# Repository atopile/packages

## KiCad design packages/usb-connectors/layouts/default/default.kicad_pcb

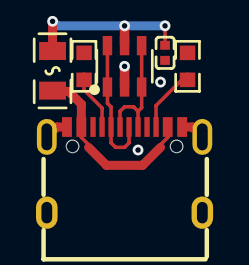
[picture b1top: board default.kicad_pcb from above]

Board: 2 copper layers, 6 parts (0 on the bottom side), 7 nets.

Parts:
C2: 0F; C0402
D1: SOT-23-6_L2.9-W1.6-P0.95-LS2.8-BL
F2: F0805
R1, R2: 10000Ω; R0603
X1: USB-C-SMD_TYPE-C-6PIN-2MD-073

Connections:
4: R1.1, X1.4
10: R2.1, X1.10
DATA_N: D1.1, D1.6, X1.5, X1.7
DATA_P: D1.3, D1.4, X1.6, X1.8
hv: F2.1, X1.2, X1.11
lv: C2.2, D1.2, R1.2, R2.2, X1.1, X1.12, X1.13, X1.14, X1.15, X1.16
power-hv: C2.1, D1.5, F2.2

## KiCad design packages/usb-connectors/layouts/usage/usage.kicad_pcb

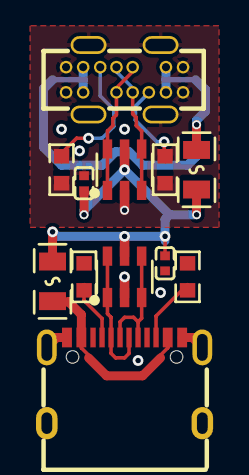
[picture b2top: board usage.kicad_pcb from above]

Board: 2 copper layers, 12 parts (0 on the bottom side), 12 nets.

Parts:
C2, C4: 0F; C0402
D1, D2: SOT-23-6_L2.9-W1.6-P0.95-LS2.8-BL
F2, F4: F0805
R1, R2, R3, R4: 10000Ω; R0603
USB1: USB-C-SMD_TYPE-C-6PIN-2MD-073
USBC1: USB-C-TH_TYPE-C-USB-14P

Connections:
4: R1.1, USB1.4
5: R4.1, USBC1.5
10: R2.1, USB1.10
12: R3.1, USBC1.12
DATA_N: D1.1, D1.6, USB1.5, USB1.7
DATA_P: D1.3, D1.4, USB1.6, USB1.8
connector-power_vbus-hv: F2.1, USB1.2, USB1.11
connector-power_vbus-hv-1: F4.1, USBC1.2, USBC1.6, USBC1.9, USBC1.13
hv: C2.1, C4.1, D1.5, D2.5, F2.2, F4.2
lv: C2.2, C4.2, D1.2, D2.2, R1.2, R2.2, R3.2, R4.2, USB1.1, USB1.12, USB1.13, USB1.14, USB1.15, USB1.16, USBC1.0, USBC1.1, USBC1.7, USBC1.8, USBC1.14, USBC1.15, USBC1.16, USBC1.17
usb_connector_vertical-usb-DATA_N: D2.1, D2.6, USBC1.3, USBC1.10
usb_connector_vertical-usb-DATA_P: D2.3, D2.4, USBC1.4, USBC1.11

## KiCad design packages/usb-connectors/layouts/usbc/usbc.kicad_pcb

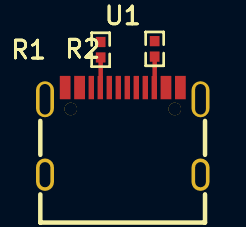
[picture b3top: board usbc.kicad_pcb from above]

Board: 2 copper layers, 3 parts (0 on the bottom side), 6 nets.

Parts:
R1, R2: 5.1kΩ ±1% 62.5mW; R0402
U1: USB-C-SMD_KH-TYPE-C-16P

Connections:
A5: R1.1, U1.A5
A6: U1.A6, U1.B6
A7: U1.A7, U1.B7
B5: R2.1, U1.B5
VBUS: U1.A4, U1.A9, U1.B4, U1.B9
gnd: R1.2, R2.2, U1.1, U1.2, U1.3, U1.4, U1.A1, U1.A12, U1.B1, U1.B12

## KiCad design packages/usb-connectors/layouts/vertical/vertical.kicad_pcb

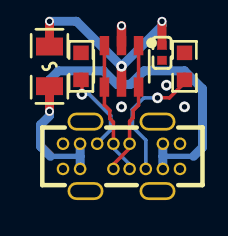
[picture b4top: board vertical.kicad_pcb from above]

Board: 2 copper layers, 6 parts (0 on the bottom side), 7 nets.

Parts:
C2: 0F; C0402
D1: SOT-23-6_L2.9-W1.6-P0.95-LS2.8-BL
F1: F0805
R1, R2: 10000Ω; R0603
X1: USB-C-TH_TYPE-C-USB-14P

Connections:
5: R2.1, X1.5
12: R1.1, X1.12
DATA_N: D1.1, D1.6, X1.3, X1.10
DATA_P: D1.3, D1.4, X1.4, X1.11
hv: F1.1, X1.2, X1.6, X1.9, X1.13
lv: C2.2, D1.2, R1.2, R2.2, X1.0, X1.1, X1.7, X1.8, X1.14, X1.15, X1.16, X1.17
power-hv: C2.1, D1.5, F1.2
